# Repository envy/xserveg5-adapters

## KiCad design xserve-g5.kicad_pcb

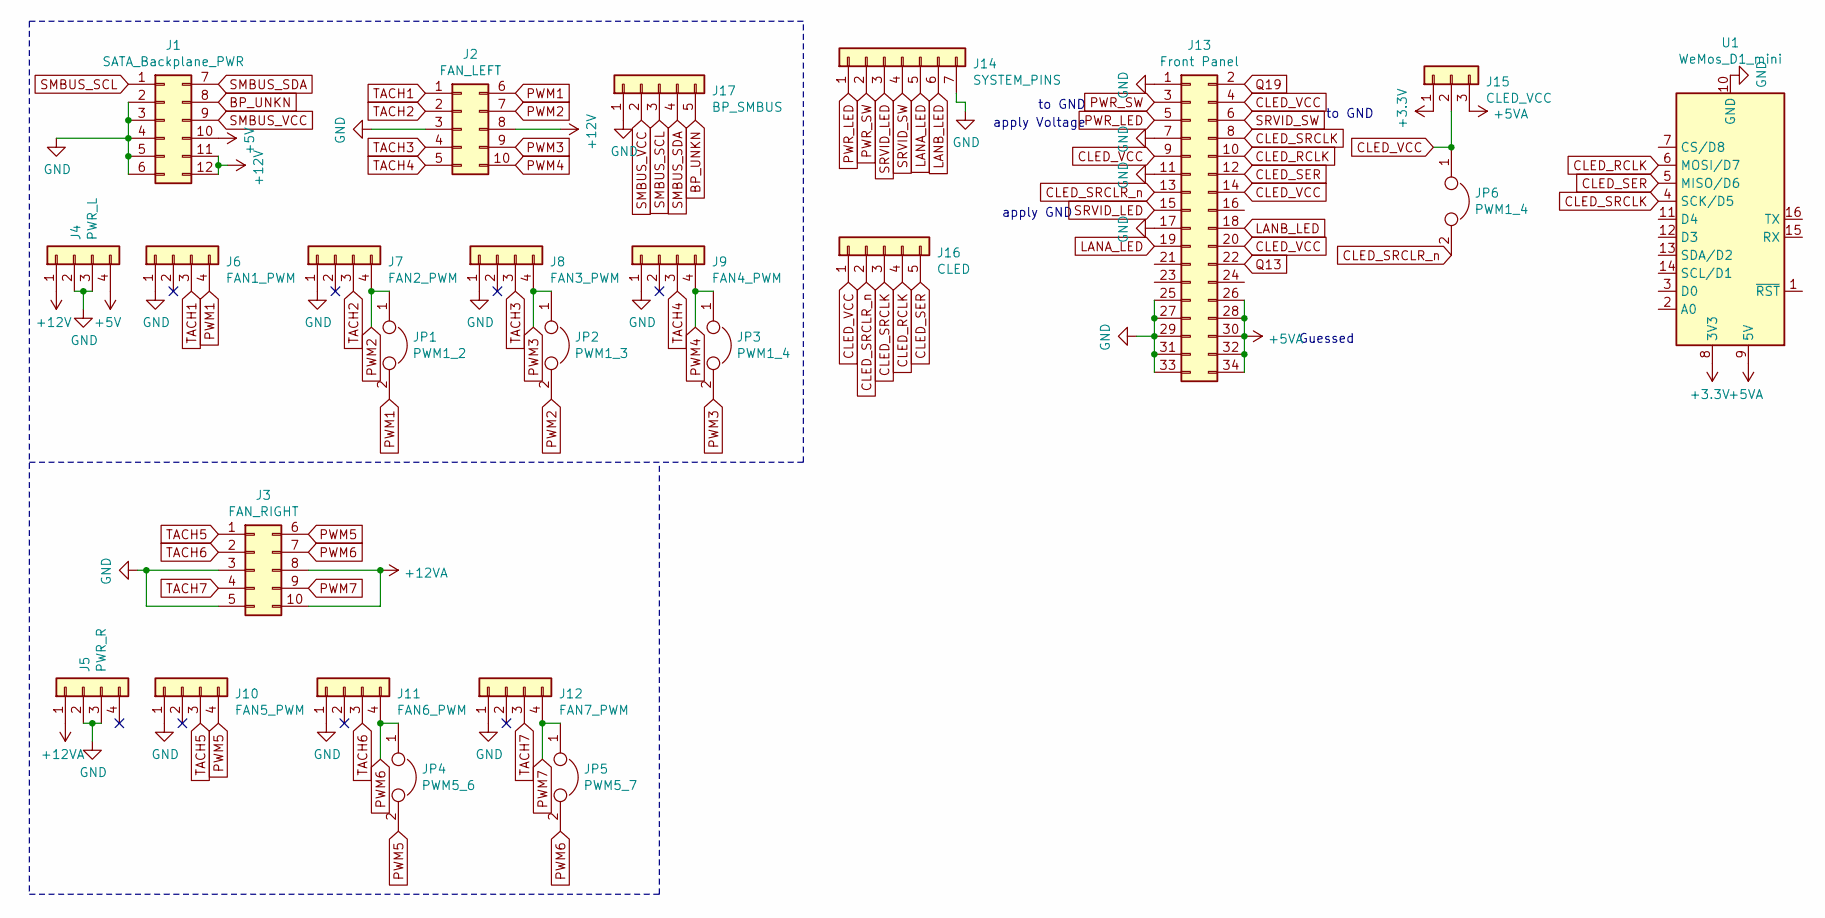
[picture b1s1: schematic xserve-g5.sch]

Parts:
J1: SATA_Backplane_PWR; Molex_Micro-Fit_3.0_43045-1212_2x06_P3.00mm_Vertical
J2: FAN_LEFT; Molex_Micro-Fit_3.0_43045-1012_2x05_P3.00mm_Vertical
J3: FAN_RIGHT; Molex_Micro-Fit_3.0_43045-1012_2x05_P3.00mm_Vertical
J4: PWR_L; TE_MATE-N-LOK_350211-1_1x04_P5.08mm_Vertical
J5: PWR_R; TE_MATE-N-LOK_350211-1_1x04_P5.08mm_Vertical
J6: FAN1_PWM; PinSocket_1x04_P2.54mm_Horizontal
J7: FAN2_PWM; PinSocket_1x04_P2.54mm_Horizontal
J8: FAN3_PWM; PinSocket_1x04_P2.54mm_Horizontal
J9: FAN4_PWM; PinSocket_1x04_P2.54mm_Horizontal
J10: FAN5_PWM; PinSocket_1x04_P2.54mm_Horizontal
J11: FAN6_PWM; PinSocket_1x04_P2.54mm_Horizontal
J12: FAN7_PWM; PinSocket_1x04_P2.54mm_Horizontal
J13: Front Panel; PinHeader_2x17_P1.27mm_Vertical; Part Harwin M50-3551742
J14: SYSTEM_PINS; PinHeader_1x07_P2.54mm_Horizontal
J15: CLED_VCC; PinHeader_1x03_P2.54mm_Vertical
J16: CLED; PinHeader_1x05_P2.54mm_Horizontal
J17: BP_SMBUS; PinHeader_1x05_P2.54mm_Horizontal
JP1: PWM1_2; PinHeader_1x02_P2.54mm_Vertical
JP2: PWM1_3; PinHeader_1x02_P2.54mm_Vertical
JP3, JP6: PWM1_4; PinHeader_1x02_P2.54mm_Vertical
JP4: PWM5_6; PinHeader_1x02_P2.54mm_Vertical
JP5: PWM5_7; PinHeader_1x02_P2.54mm_Vertical
U1: WeMos_D1_mini; WEMOS_D1_mini_light

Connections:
+3V3: J15.1, U1.8 (3V3)
+5V: J1.10, J4.4
+5VA: J13.26, J13.28, J13.30, J13.32, J13.34, J15.3, U1.9 (5V)
+12V: J1.11, J1.12, J2.8, J4.1
+12VA: J3.8, J3.10, J5.1
BP_UNKN: J1.8, J17.5
CLED_RCLK: J13.10, J16.4, U1.6 (MOSI/D7)
CLED_SER: J13.12, J16.5, U1.5 (MISO/D6)
CLED_SRCLK: J13.8, J16.3, U1.4 (SCK/D5)
CLED_SRCLR_n: J13.13, J16.2, JP6.2
CLED_VCC: J13.4, J13.9, J13.14, J13.20, J15.2, J16.1, JP6.1
GND: J1.2, J1.3, J1.4, J1.5, J1.6, J2.3, J3.3, J3.5, J4.2, J4.3, J5.2, J5.3, J6.1, J7.1, J8.1, J9.1, J10.1, J11.1, J12.1, J13.1, J13.7, J13.11, J13.17, J13.25, J13.27, J13.29, J13.31, J13.33, J14.7, J17.1, U1.10 (GND)
LANA_LED: J13.19, J14.5
LANB_LED: J13.18, J14.6
PWM1: J2.6, J6.4, JP1.2
PWM2: J2.7, J7.4, JP1.1, JP2.2
PWM3: J2.9, J8.4, JP2.1, JP3.2
PWM4: J2.10, J9.4, JP3.1
PWM5: J3.6, J10.4, JP4.2
PWM6: J3.7, J11.4, JP4.1, JP5.2
PWM7: J3.9, J12.4, JP5.1
PWR_LED: J13.5, J14.1
PWR_SW: J13.3, J14.2
Q13: J13.22
Q19: J13.2
SMBUS_SCL: J1.1, J17.3
SMBUS_SDA: J1.7, J17.4
SMBUS_VCC: J1.9, J17.2
SRVID_LED: J13.15, J14.3
SRVID_SW: J13.6, J14.4
TACH1: J2.1, J6.3
TACH2: J2.2, J7.3
TACH3: J2.4, J8.3
TACH4: J2.5, J9.3
TACH5: J3.1, J10.3
TACH6: J3.2, J11.3
TACH7: J3.4, J12.3

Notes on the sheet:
Guessed
to GND
apply Voltage
apply GND

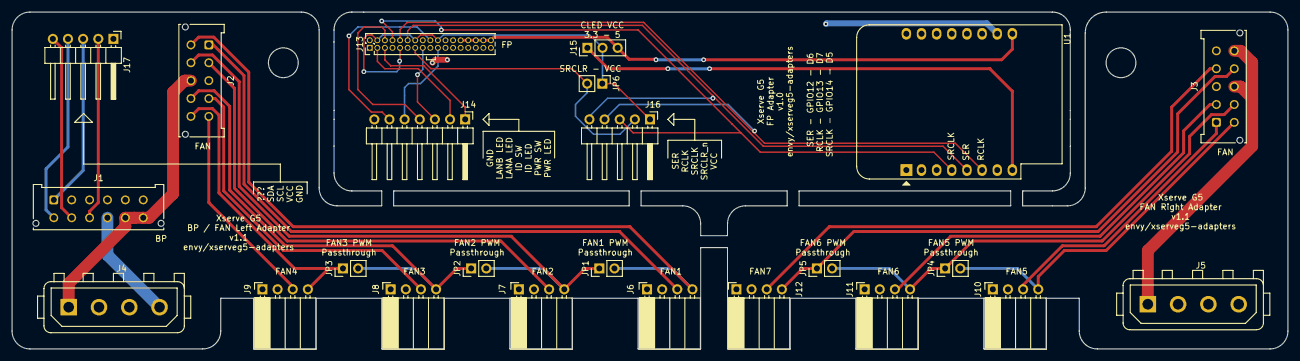
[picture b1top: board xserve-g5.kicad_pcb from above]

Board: 2 copper layers, 214.0 x 56.5 mm, 24 parts (0 on the bottom side), 35 nets.

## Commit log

2020-08-14 first version
2020-09-29 Switch pwm and tacho pins...
